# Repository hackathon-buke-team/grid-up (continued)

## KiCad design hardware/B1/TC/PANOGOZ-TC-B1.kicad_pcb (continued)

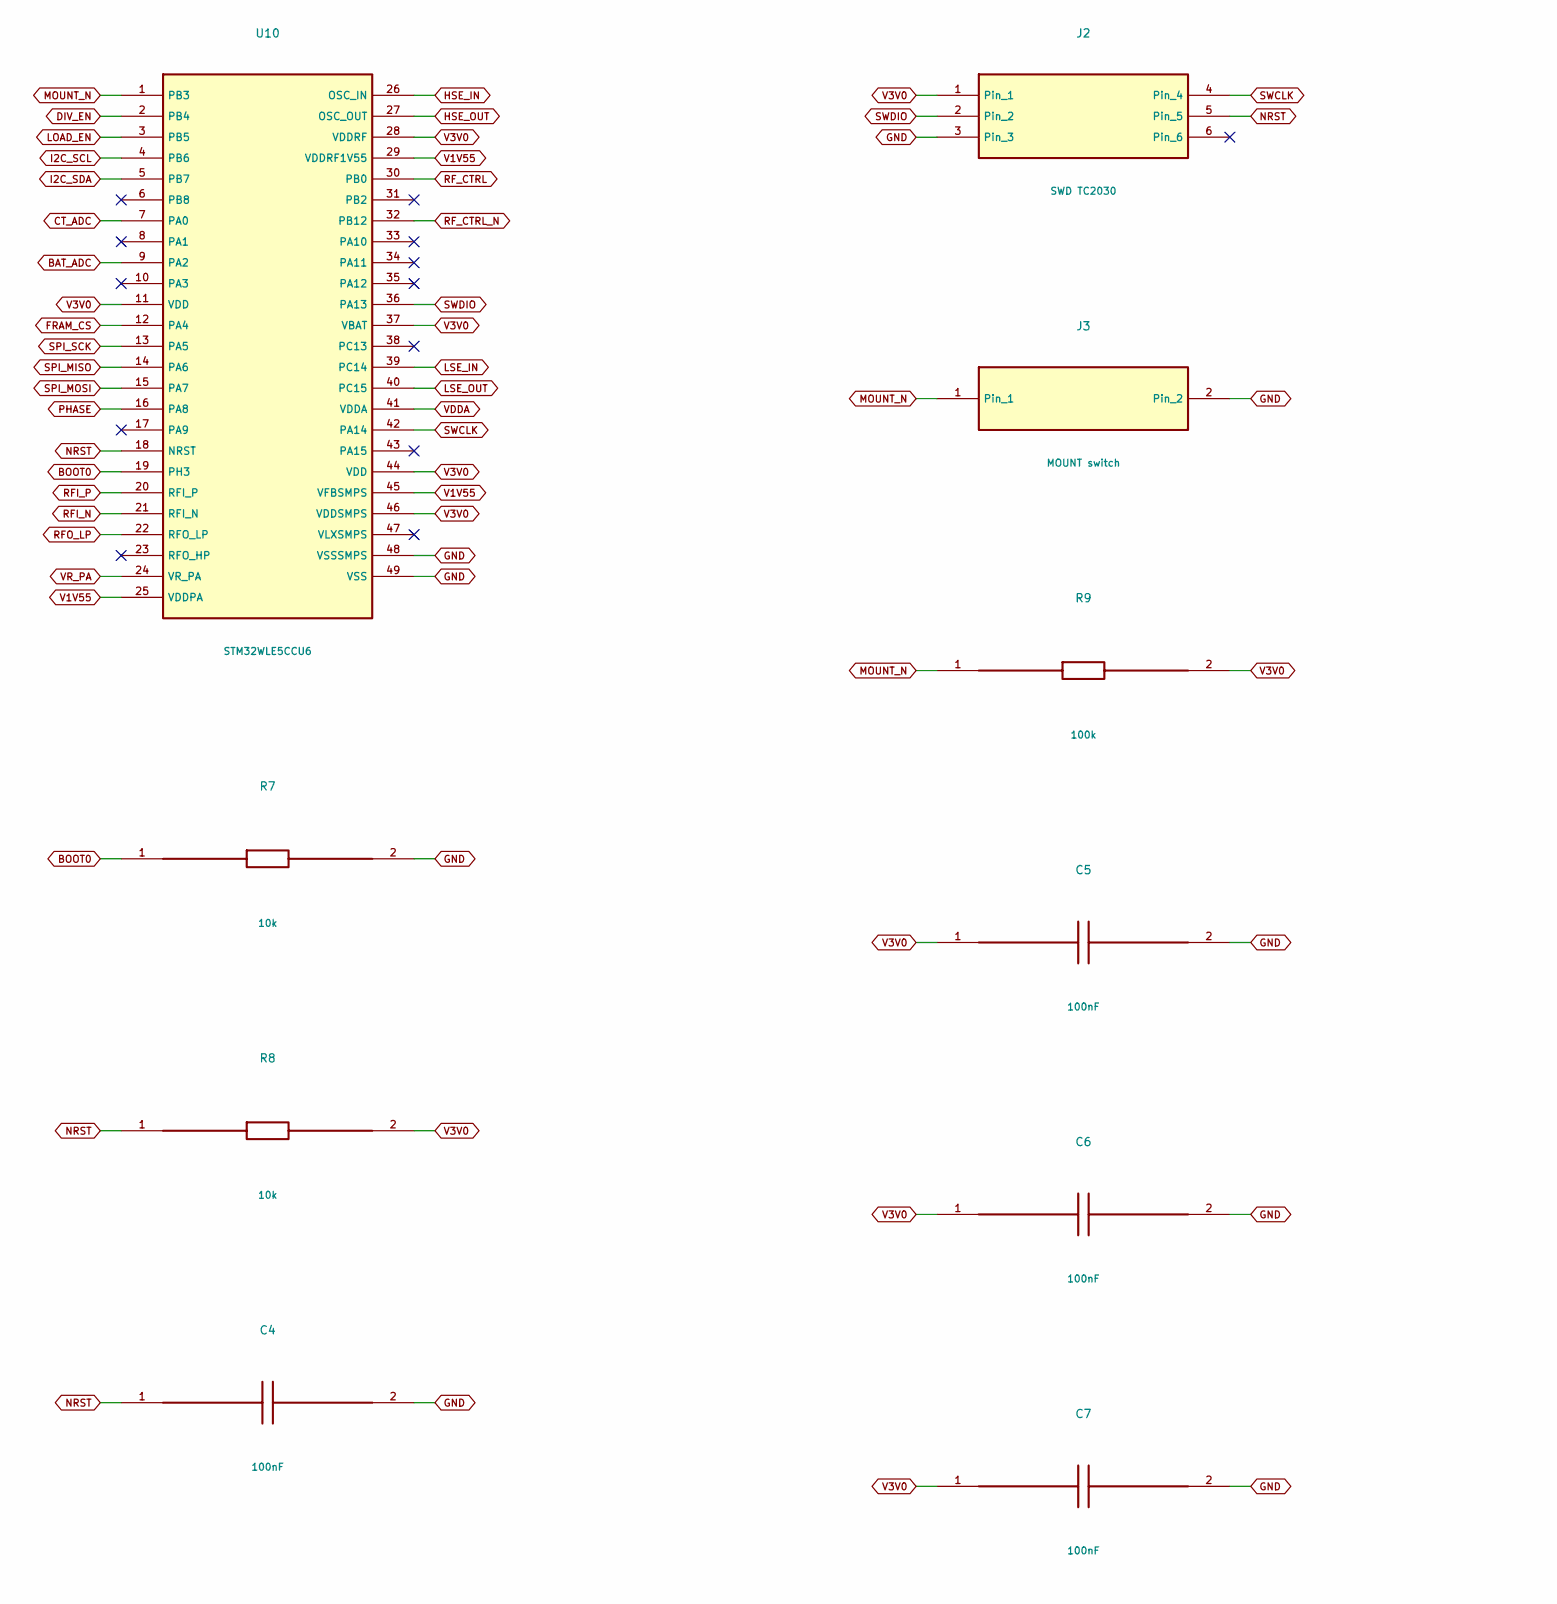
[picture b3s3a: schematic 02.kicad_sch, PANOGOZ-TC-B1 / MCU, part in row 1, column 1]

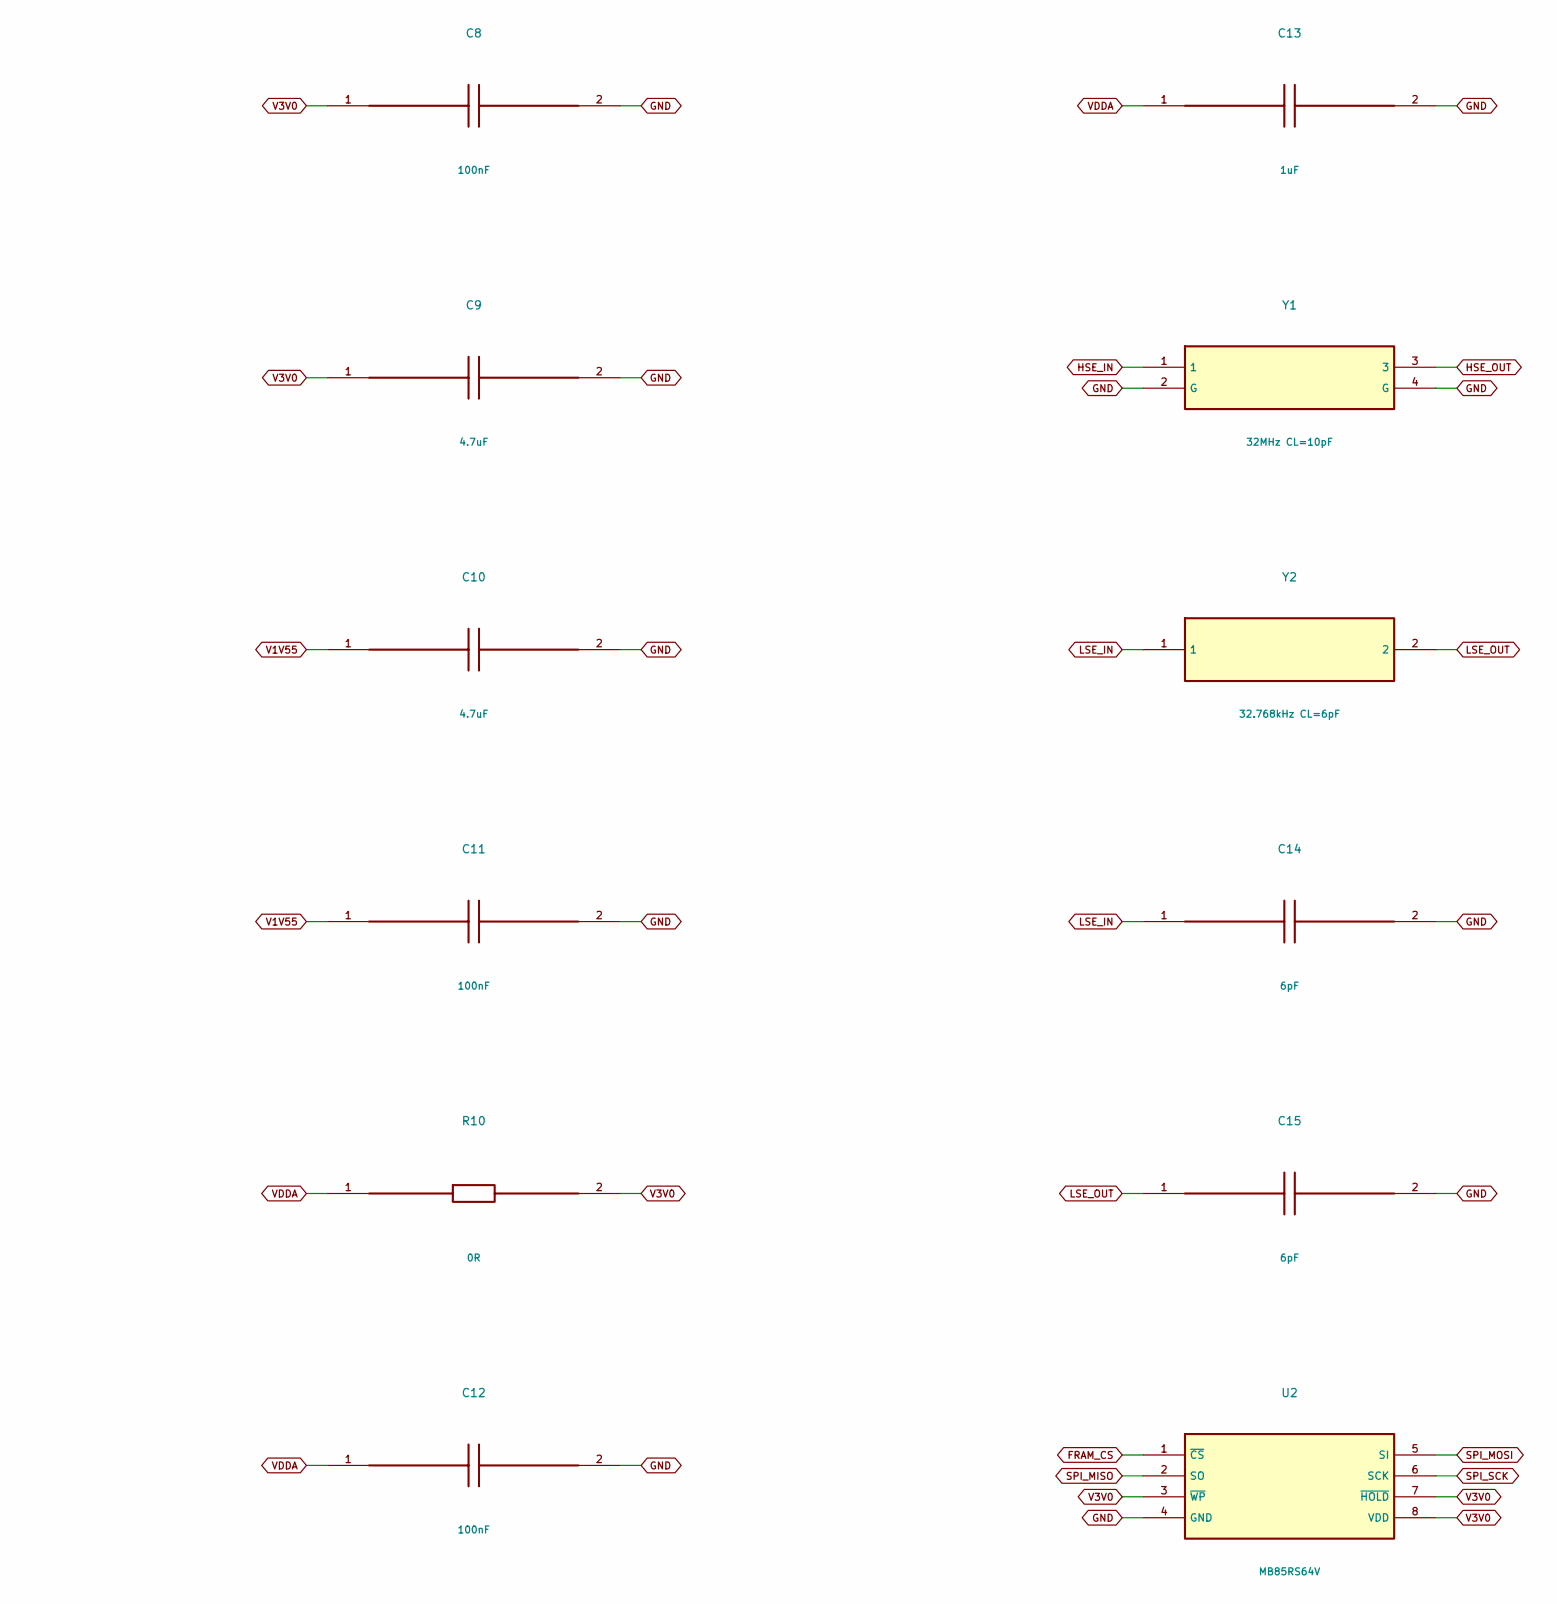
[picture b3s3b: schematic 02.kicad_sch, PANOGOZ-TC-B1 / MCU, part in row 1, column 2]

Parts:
C4, C5, C6, C7, C8, C11, C12: 100nF; C_0402_1005Metric; MPN X7R 16V 100nF
C9, C10: 4.7uF; C_0402_1005Metric; MPN X7R 16V 4.7uF
C13: 1uF; C_0402_1005Metric; MPN X7R 16V 1uF
C14, C15: 6pF; C_0402_1005Metric; MPN X7R 16V 6pF
J2: SWD TC2030; Tag-Connect_TC2030-IDC-NL_2x03_P1.27mm_Vertical; MPN SWD TC2030
J3: MOUNT switch; JST_SH_SM02B-SRSS-TB_1x02-1MP_P1.00mm_Horizontal; MPN MOUNT switch
R7, R8: 10k; R_0402_1005Metric; MPN 1% thick film 10k
R9: 100k; R_0402_1005Metric; MPN 1% thick film 100k
R10: 0R; R_0402_1005Metric; MPN 1% thick film 0R
U2: MB85RS64V; SOIC-8_3.9x4.9mm_P1.27mm; MPN MB85RS64V
U10: STM32WLE5CCU6; QFN-48-1EP_7x7mm_P0.5mm_EP5.6x5.6mm; MPN STM32WLE5CCU6
Y1: 32MHz CL=10pF; Crystal_SMD_3225-4Pin_3.2x2.5mm; MPN 32MHz CL=10pF
Y2: 32.768kHz CL=6pF; Crystal_SMD_3215-2Pin_3.2x1.5mm; MPN 32.768kHz CL=6pF

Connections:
BAT_ADC: U10.9 (PA2); also elsewhere on the board
BOOT0: R7.1, U10.19 (PH3)
CT_ADC: U10.7 (PA0); also elsewhere on the board
DIV_EN: U10.2 (PB4); also elsewhere on the board
FRAM_CS: U2.1 (~CS), U10.12 (PA4); also elsewhere on the board
GND: C4.2, C5.2, C6.2, C7.2, C8.2, C9.2, C10.2, C11.2, C12.2, C13.2, C14.2, C15.2, J2.3, J3.2, R7.2, U2.4 (GND), U10.48 (VSSSMPS), U10.49 (VSS), Y1.2 (G), Y1.4 (G); also elsewhere on the board
HSE_IN: U10.26 (OSC_IN), Y1.1
HSE_OUT: U10.27 (OSC_OUT), Y1.3
I2C_SCL: U10.4 (PB6); also elsewhere on the board
I2C_SDA: U10.5 (PB7); also elsewhere on the board
LOAD_EN: U10.3 (PB5); also elsewhere on the board
LSE_IN: C14.1, U10.39 (PC14), Y2.1
LSE_OUT: C15.1, U10.40 (PC15), Y2.2
MOUNT_N: J3.1, R9.1, U10.1 (PB3)
NRST: C4.1, J2.5, R8.1, U10.18 (NRST)
PHASE: U10.16 (PA8); also elsewhere on the board
RFI_N: U10.21 (RFI_N); also elsewhere on the board
RFI_P: U10.20 (RFI_P); also elsewhere on the board
RFO_LP: U10.22 (RFO_LP); also elsewhere on the board
RF_CTRL: U10.30 (PB0); also elsewhere on the board
RF_CTRL_N: U10.32 (PB12); also elsewhere on the board
SPI_MISO: U2.2 (SO), U10.14 (PA6)
SPI_MOSI: U2.5 (SI), U10.15 (PA7)
SPI_SCK: U2.6 (SCK), U10.13 (PA5)
SWCLK: J2.4, U10.42 (PA14)
SWDIO: J2.2, U10.36 (PA13)
V1V55: C10.1, C11.1, U10.25 (VDDPA), U10.29 (VDDRF1V55), U10.45 (VFBSMPS)
V3V0: C5.1, C6.1, C7.1, C8.1, C9.1, J2.1, R8.2, R9.2, R10.2, U2.3 (~WP), U2.7 (~HOLD), U2.8 (VDD), U10.11 (VDD), U10.28 (VDDRF), U10.37 (VBAT), U10.44 (VDD), U10.46 (VDDSMPS); also elsewhere on the board
VDDA: C12.1, C13.1, R10.1, U10.41 (VDDA)
VR_PA: U10.24 (VR_PA); also elsewhere on the board

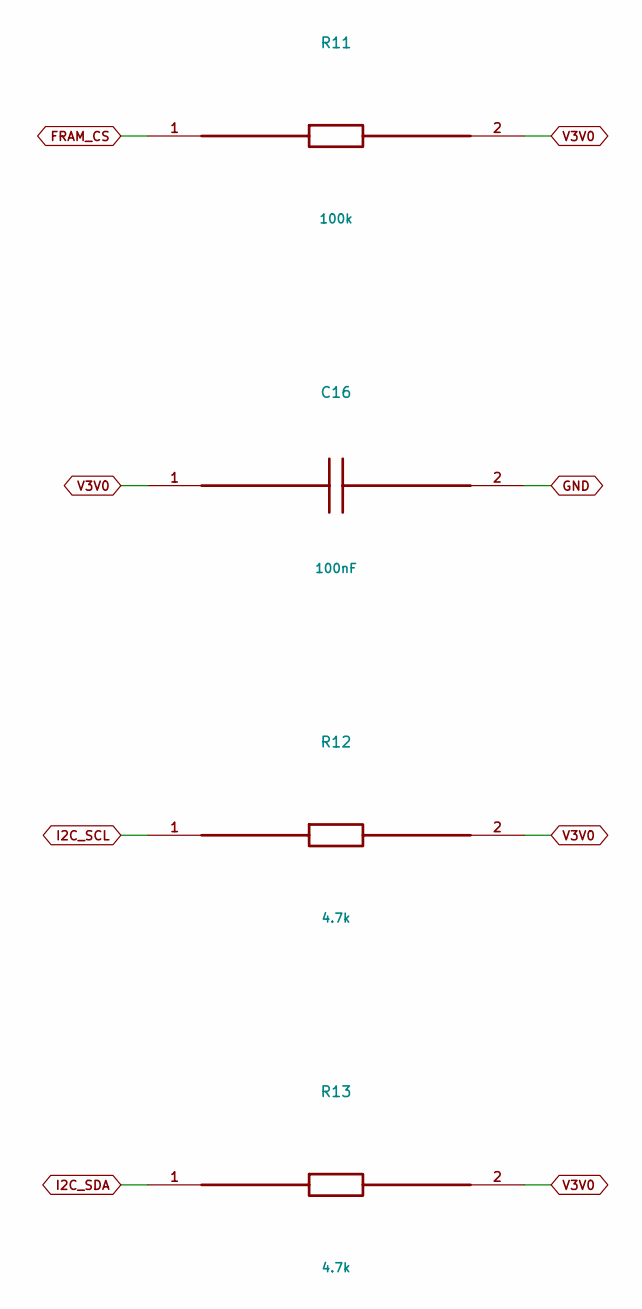
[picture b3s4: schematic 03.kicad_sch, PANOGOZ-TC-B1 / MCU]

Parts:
C16: 100nF; C_0402_1005Metric; MPN X7R 16V 100nF
R11: 100k; R_0402_1005Metric; MPN 1% thick film 100k
R12, R13: 4.7k; R_0402_1005Metric; MPN 1% thick film 4.7k

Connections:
FRAM_CS: R11.1; also elsewhere on the board
GND: C16.2; also elsewhere on the board
I2C_SCL: R12.1; also elsewhere on the board
I2C_SDA: R13.1; also elsewhere on the board
V3V0: C16.1, R11.2, R12.2, R13.2; also elsewhere on the board

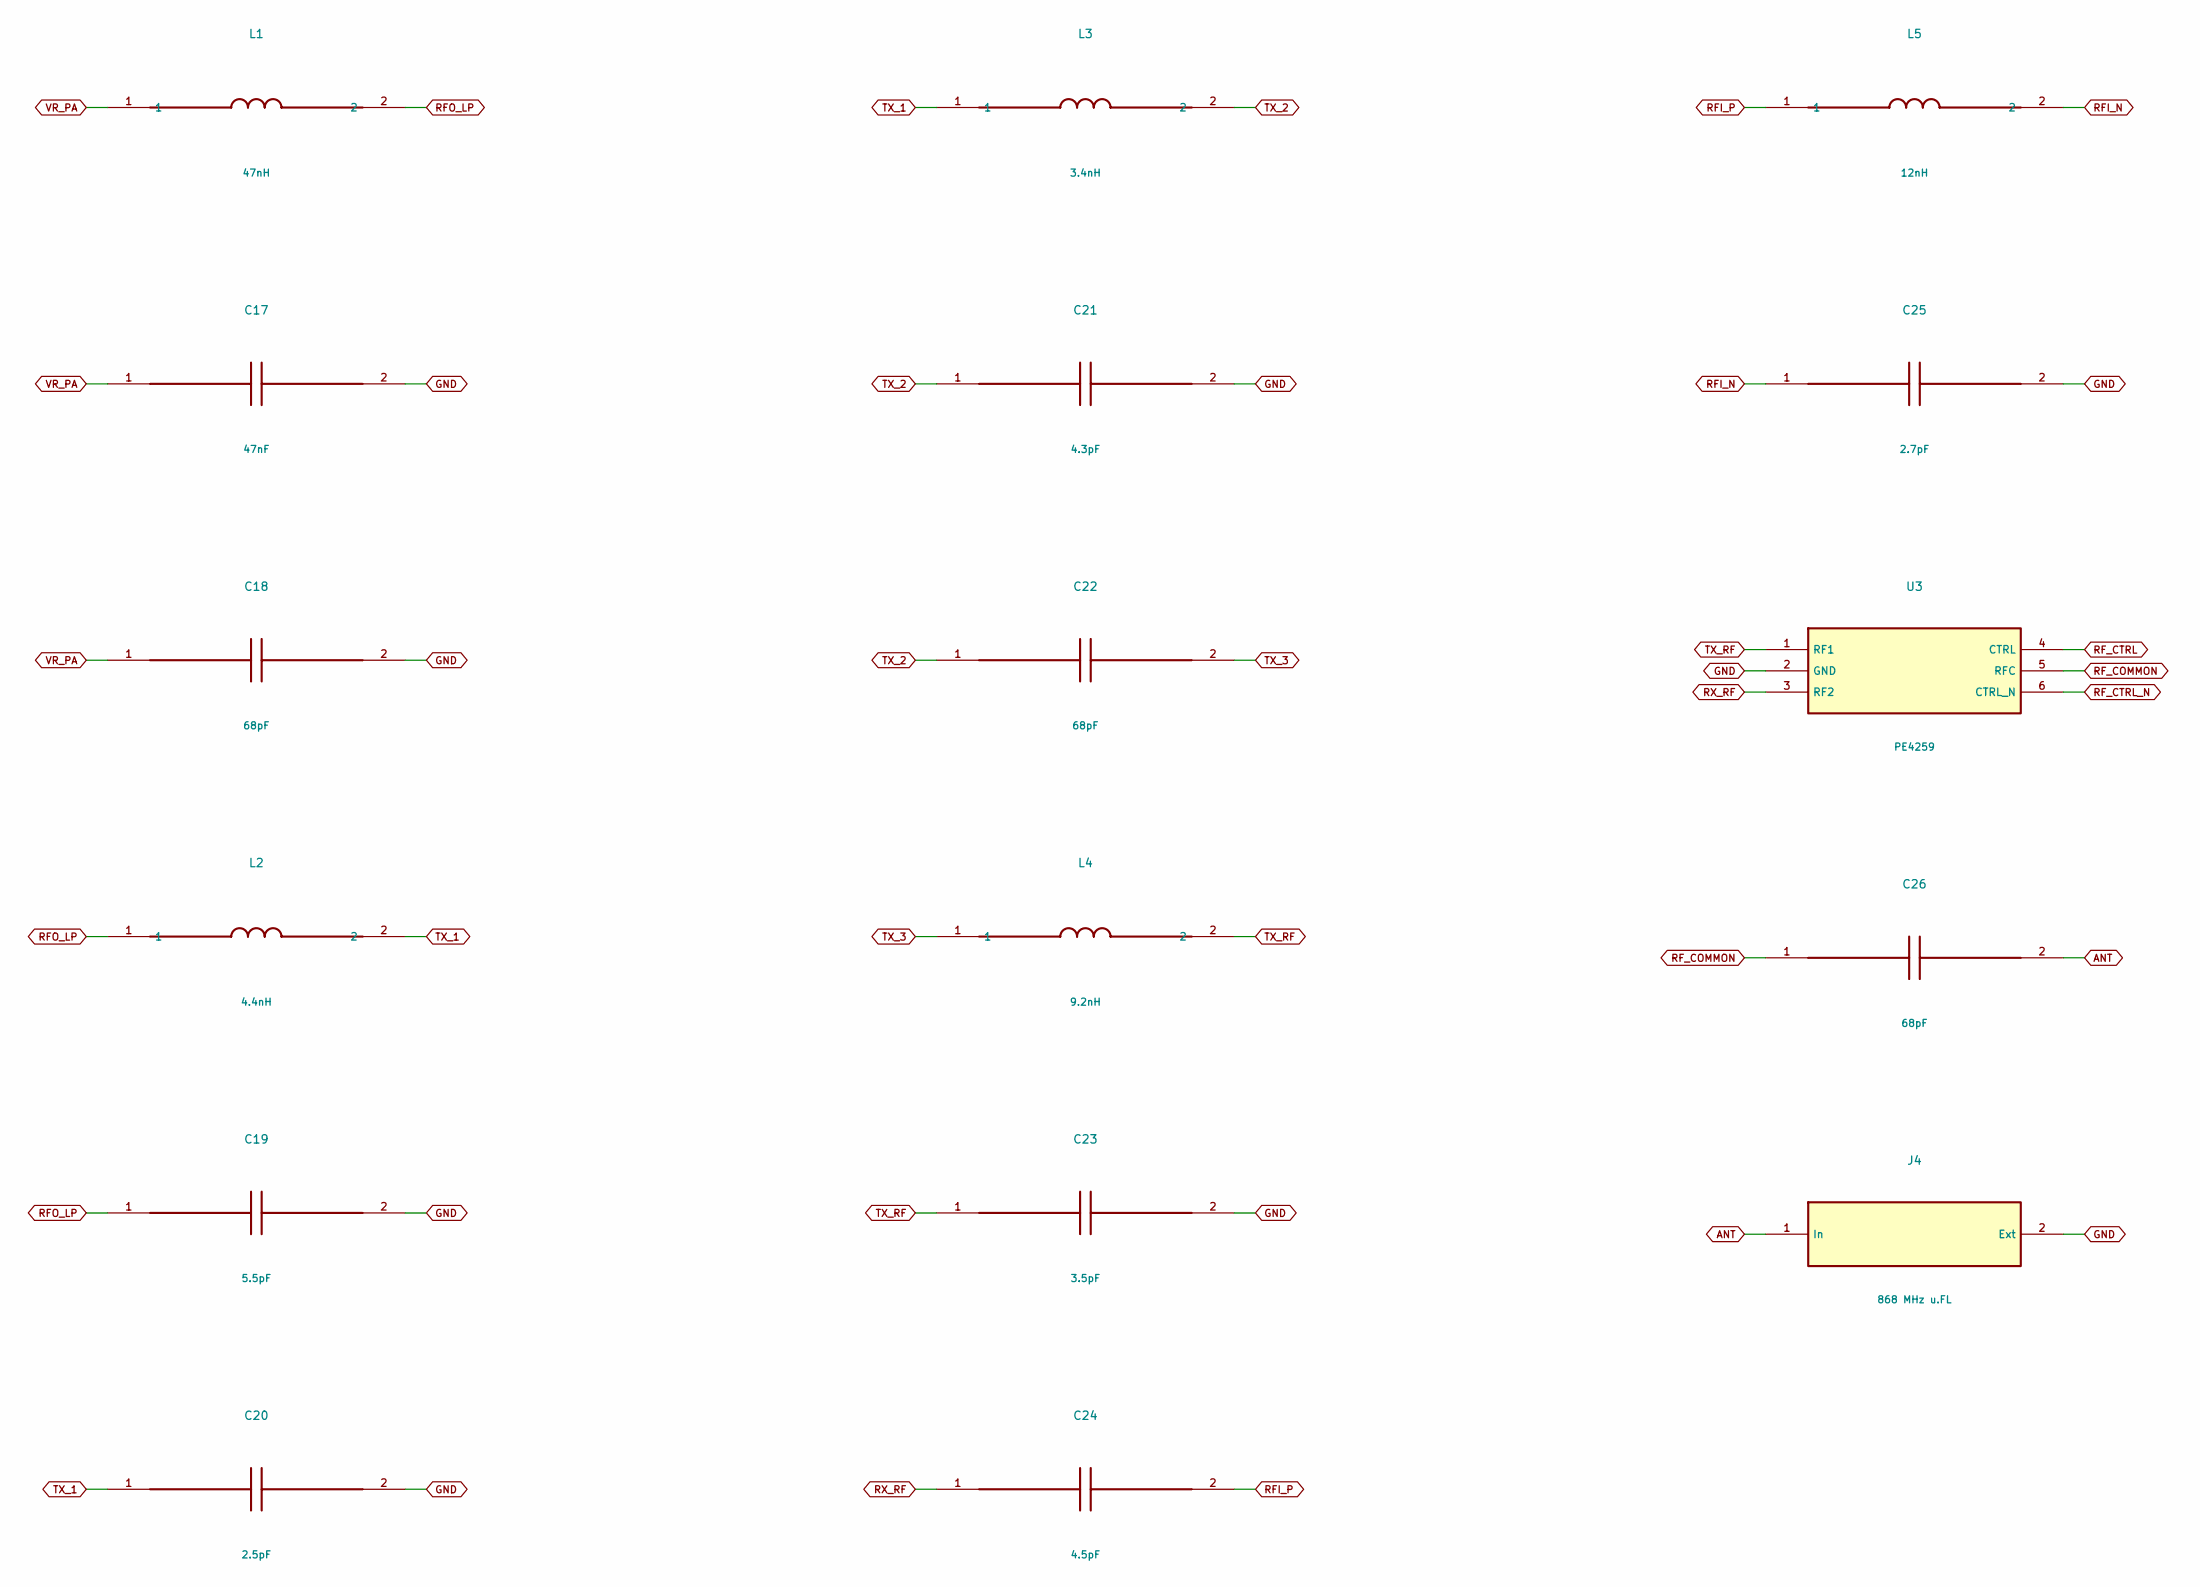
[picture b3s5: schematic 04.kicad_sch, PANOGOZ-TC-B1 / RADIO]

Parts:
C17: 47nF; C_0402_1005Metric; MPN X7R 16V 47nF
C18, C22, C26: 68pF; C_0402_1005Metric; MPN X7R 16V 68pF
C19: 5.5pF; C_0402_1005Metric; MPN X7R 16V 5.5pF
C20: 2.5pF; C_0402_1005Metric; MPN X7R 16V 2.5pF
C21: 4.3pF; C_0402_1005Metric; MPN X7R 16V 4.3pF
C23: 3.5pF; C_0402_1005Metric; MPN X7R 16V 3.5pF
C24: 4.5pF; C_0402_1005Metric; MPN X7R 16V 4.5pF
C25: 2.7pF; C_0402_1005Metric; MPN X7R 16V 2.7pF
J4: 868 MHz u.FL; U.FL_Hirose_U.FL-R-SMT-1_Vertical; MPN 868 MHz u.FL
L1: 47nH; L_0402_1005Metric; MPN 47nH
L2: 4.4nH; L_0402_1005Metric; MPN 4.4nH
L3: 3.4nH; L_0402_1005Metric; MPN 3.4nH
L4: 9.2nH; L_0402_1005Metric; MPN 9.2nH
L5: 12nH; L_0402_1005Metric; MPN 12nH
U3: PE4259; SOT-363_SC-70-6; MPN PE4259

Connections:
ANT: C26.2, J4.1 (In)
GND: C17.2, C18.2, C19.2, C20.2, C21.2, C23.2, C25.2, J4.2 (Ext), U3.2 (GND); also elsewhere on the board
RFI_N: C25.1, L5.2; also elsewhere on the board
RFI_P: C24.2, L5.1; also elsewhere on the board
RFO_LP: C19.1, L1.2, L2.1; also elsewhere on the board
RF_COMMON: C26.1, U3.5 (RFC)
RF_CTRL: U3.4 (CTRL); also elsewhere on the board
RF_CTRL_N: U3.6 (CTRL_N); also elsewhere on the board
RX_RF: C24.1, U3.3 (RF2)
TX_1: C20.1, L2.2, L3.1
TX_2: C21.1, C22.1, L3.2
TX_3: C22.2, L4.1
TX_RF: C23.1, L4.2, U3.1 (RF1)
VR_PA: C17.1, C18.1, L1.1; also elsewhere on the board

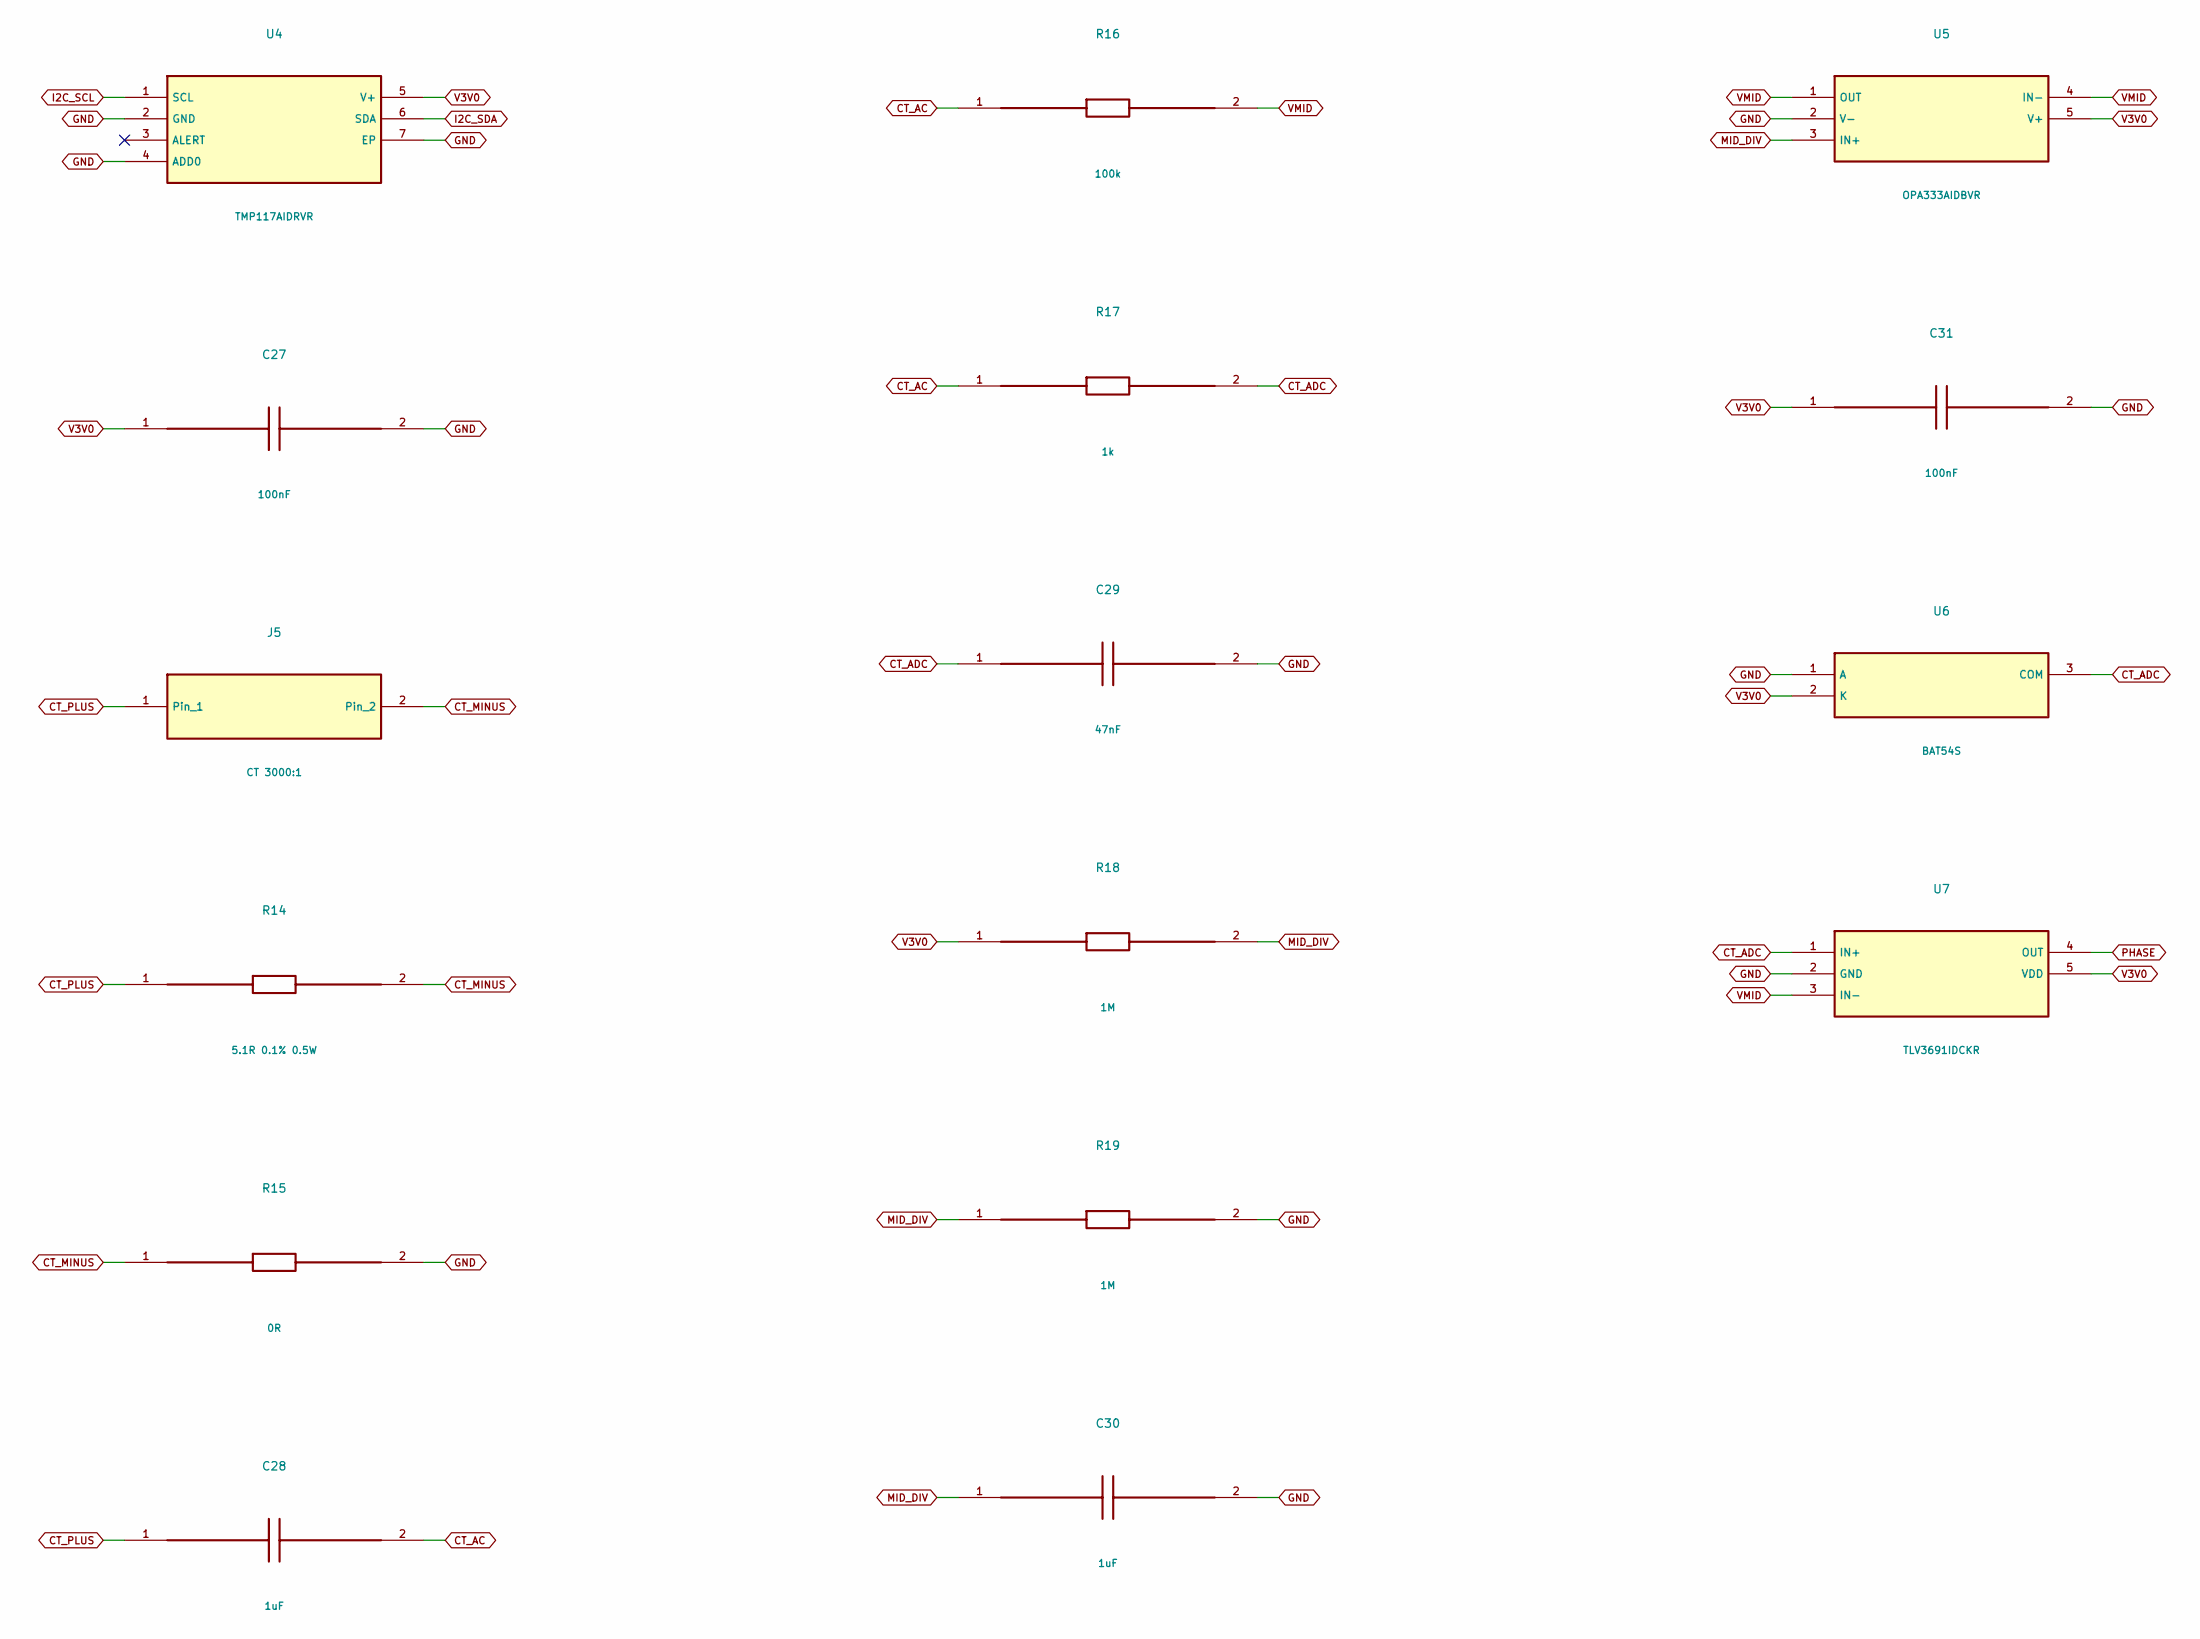
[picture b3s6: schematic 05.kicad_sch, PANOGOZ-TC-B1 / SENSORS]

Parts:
C27, C31: 100nF; C_0402_1005Metric; MPN X7R 16V 100nF
C28, C30: 1uF; C_0402_1005Metric; MPN X7R 16V 1uF
C29: 47nF; C_0402_1005Metric; MPN X7R 16V 47nF
J5: CT 3000:1; JST_SH_SM02B-SRSS-TB_1x02-1MP_P1.00mm_Horizontal; MPN CT 3000:1
R14: 5.1R 0.1% 0.5W; R_1210_3225Metric; MPN 1% thick film 5.1R 0.1% 0.5W
R15: 0R; R_0402_1005Metric; MPN 1% thick film 0R
R16: 100k; R_0402_1005Metric; MPN 1% thick film 100k
R17: 1k; R_0402_1005Metric; MPN 1% thick film 1k
R18, R19: 1M; R_0402_1005Metric; MPN 1% thick film 1M
U4: TMP117AIDRVR; WSON-6-1EP_2x2mm_P0.65mm_EP1x1.6mm; MPN TMP117AIDRVR
U5: OPA333AIDBVR; SOT-23-5; MPN OPA333AIDBVR
U6: BAT54S; SOT-23; MPN BAT54S
U7: TLV3691IDCKR; SOT-353_SC-70-5; MPN TLV3691IDCKR

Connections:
CT_AC: C28.2, R16.1, R17.1
CT_ADC: C29.1, R17.2, U6.3 (COM), U7.1 (IN+); also elsewhere on the board
CT_MINUS: J5.2, R14.2, R15.1
CT_PLUS: C28.1, J5.1, R14.1
GND: C27.2, C29.2, C30.2, C31.2, R15.2, R19.2, U4.2 (GND), U4.4 (ADD0), U4.7 (EP), U5.2 (V-), U6.1 (A), U7.2 (GND); also elsewhere on the board
I2C_SCL: U4.1 (SCL); also elsewhere on the board
I2C_SDA: U4.6 (SDA); also elsewhere on the board
MID_DIV: C30.1, R18.2, R19.1, U5.3 (IN+)
PHASE: U7.4 (OUT); also elsewhere on the board
V3V0: C27.1, C31.1, R18.1, U4.5 (V+), U5.5 (V+), U6.2 (K), U7.5 (VDD); also elsewhere on the board
VMID: R16.2, U5.1 (OUT), U5.4 (IN-), U7.3 (IN-)

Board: 4 copper layers, 73 parts (27 on the bottom side), 46 nets, no tracks yet.

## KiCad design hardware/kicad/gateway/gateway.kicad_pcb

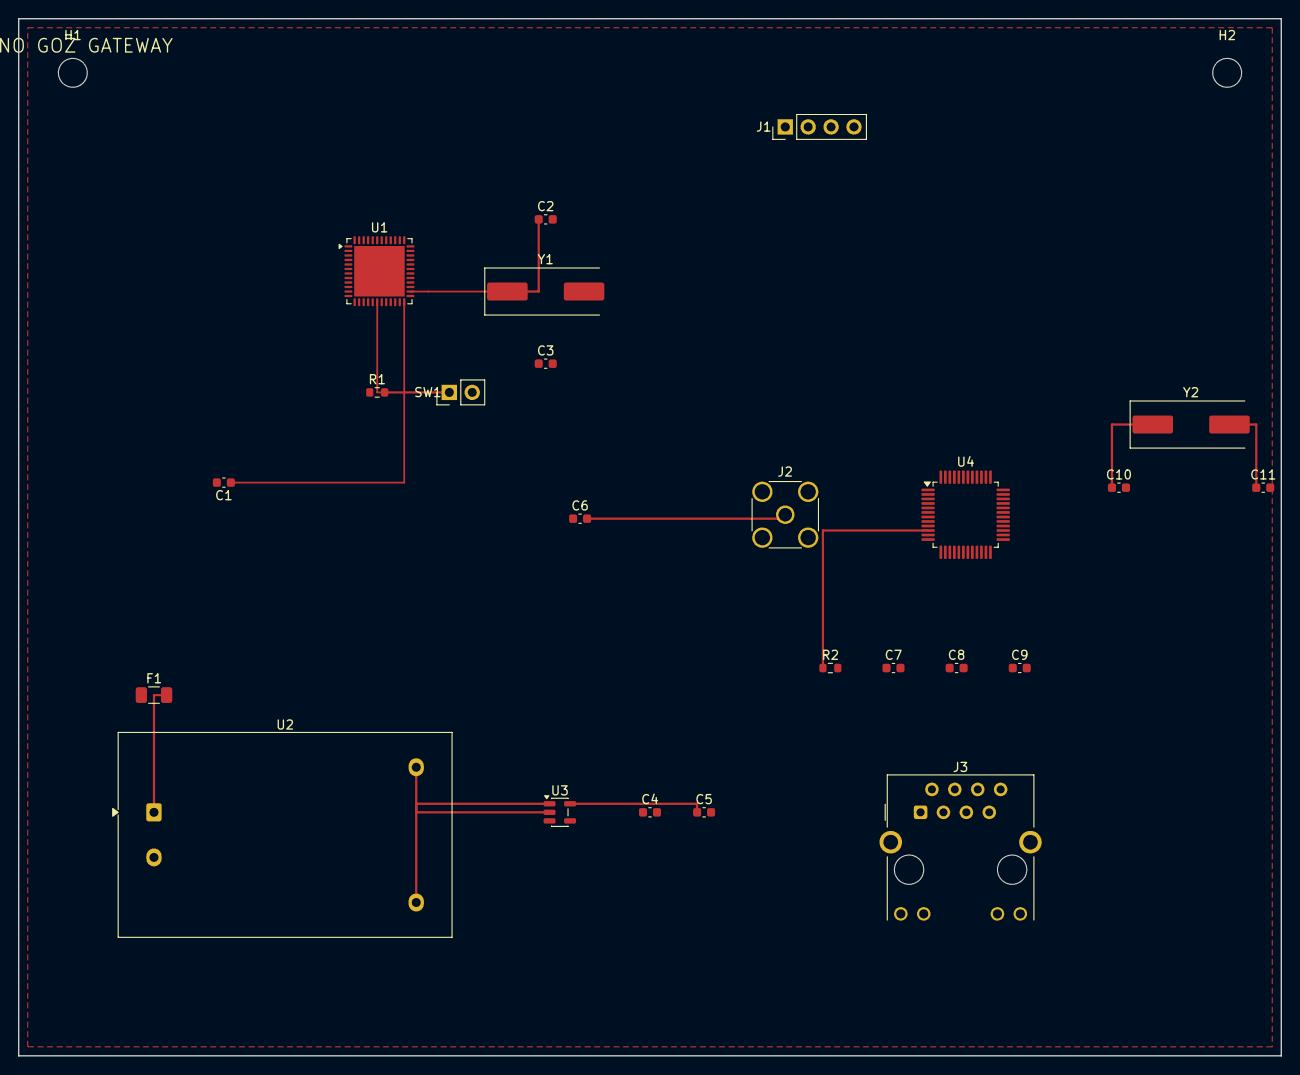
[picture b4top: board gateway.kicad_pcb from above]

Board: 2 copper layers, 140.0 x 115.0 mm, 26 parts (0 on the bottom side), 29 nets.

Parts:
C1: 100nF; C_0603_1608Metric
C2, C3: 12pF; C_0603_1608Metric
C4: 10uF; C_0603_1608Metric
C5: 1uF; C_0603_1608Metric
C6: 2.2pF match; C_0603_1608Metric
C7: 2.2uF (TOCAP); C_0603_1608Metric
C8: 0.1uF (VBG); C_0603_1608Metric
C9: 1uF (1V2O); C_0603_1608Metric
C10, C11: 18pF; C_0603_1608Metric
F1: 0.5A (modul dali); Fuse_1206_3216Metric
H1, H2: MountingHole_3.2mm_M3
J1: SWD; PinHeader_1x04_P2.54mm_Vertical
J2: SMA (harici anten); SMA_Amphenol_132134_Vertical
J3: RJ45 (magnetics harici); RJ45_Hanrun_HR911105A_Horizontal
R1: 10k; R_0603_1608Metric
R2: 12k 1% (EXRES1 bias); R_0603_1608Metric
SW1: RESET(SW_Push); PinHeader_1x02_P2.54mm_Vertical
U1: STM32WLE5CCUx; QFN-48-1EP_7x7mm_P0.5mm_EP5.6x5.6mm
U2: HLK-PM01; Converter_ACDC_Hi-Link_HLK-PMxx
U3: AP2112K-3.3; SOT-23-5
U4: W5500; LQFP-48_7x7mm_P0.5mm
Y1: 32MHz; Crystal_SMD_HC49-SD
Y2: 25MHz (W5500); Crystal_SMD_HC49-SD

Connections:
1V2O: C9.1, U4.22
+3V3: C5.1, J1.4, R1.1, U1.11, U1.25, U1.28, U1.29, U1.37, U1.41, U1.44, U1.45, U1.46, U3.5, U4.4, U4.28
AC_L: F1.2, U2.1
ANT: C6.2, J2.1
ETH_CS: U1.17, U4.32
ETH_INT: U1.34, U4.36
ETH_MISO: U1.13, U4.34
ETH_MOSI: U1.33, U4.35
ETH_RST: U1.35, U4.37
ETH_RXN: J3.4, U4.5
ETH_RXP: J3.3, U4.6
ETH_SCLK: U1.16, U4.33
ETH_TXN: J3.2, U4.1
ETH_TXP: J3.1, U4.2
ETH_XI: C10.1, U4.30, Y2.1
ETH_XO: C11.1, U4.31, Y2.2
EXRES1: R2.1, U4.10
GND: C1.2, C2.2, C3.2, C5.2, C7.2, C8.2, C9.2, C10.2, C11.2, J1.3, J2.2, R2.2, SW1.2, U1.48, U1.49, U4.3, U4.29, U4.43, U4.44, U4.45
GND5V: C4.2, U2.3, U3.2
NRST: R1.2, SW1.1, U1.18
OSC_IN: C2.1, U1.26, Y1.1
OSC_OUT: C3.1, U1.27, Y1.2
RF_HP: C6.1, U1.23
SWCLK: J1.2, U1.42
SWDIO: J1.1, U1.36
TOCAP: C7.1, U4.20
V5: C4.1, U2.4, U3.1, U3.3
VBG: C8.1, U4.18
VRPA: C1.1, U1.24
